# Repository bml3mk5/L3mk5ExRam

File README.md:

# External Memory Card For HITACHI BASIC MASTER LEVEL3 mark5

This is the external memory card for HITACHI BASIC MASTER LEVEL3 mark5 (MB-6892/A).

* This card is not able to use on BASIC MASTER LEVEL3 (MB-6890) and MarkII (MB-6891).

## Used Tools

* EAGLE 9.6

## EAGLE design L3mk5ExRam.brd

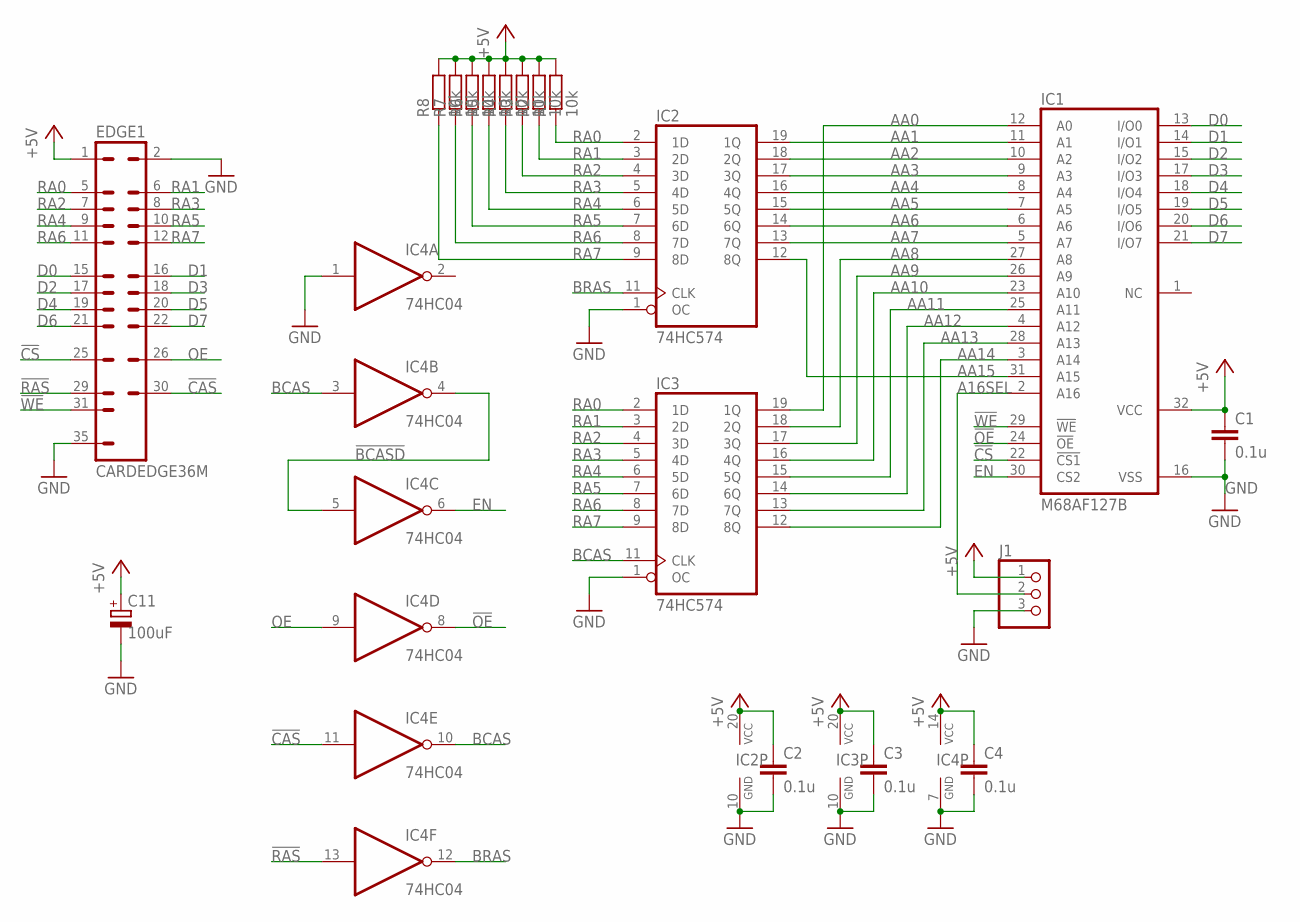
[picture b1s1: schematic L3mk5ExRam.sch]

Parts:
C1, C2, C3, C4: 0.1u; C025-024X044
C11: 100uF; E2-5
EDGE1: CARDEDGE36M; PM
IC1: M68AF127B; SOJ32-400
IC2, IC3: 74HC574; DIL20
IC4: 74HC04; DIL14
J1: PINHD-1X3; 1X03
R1, R2, R3, R4, R5, R6, R7, R8: 10k; 0204V

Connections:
!BCASD: IC4.4 (O), IC4.5 (I)
!CAS: EDGE1.30, IC4.11 (I)
!CS: EDGE1.25, IC1.22 (!CS1)
!OE: IC1.24 (!OE), IC4.8 (O)
!RAS: EDGE1.29, IC4.13 (I)
!WE: EDGE1.31, IC1.29 (!WE)
+5V: C1.1, C2.1, C3.1, C4.1, C11.+, EDGE1.1, IC1.32 (VCC), IC2.20 (VCC), IC3.20 (VCC), IC4.14 (VCC), J1.1, R1.2, R2.2, R3.2, R4.2, R5.2, R6.2, R7.2, R8.2
A16SEL: IC1.2 (A16), J1.2
AA0: IC1.12 (A0), IC3.19 (1Q)
AA1: IC1.11 (A1), IC2.19 (1Q)
AA2: IC1.10 (A2), IC2.18 (2Q)
AA3: IC1.9 (A3), IC2.17 (3Q)
AA4: IC1.8 (A4), IC2.16 (4Q)
AA5: IC1.7 (A5), IC2.15 (5Q)
AA6: IC1.6 (A6), IC2.14 (6Q)
AA7: IC1.5 (A7), IC2.13 (7Q)
AA8: IC1.27 (A8), IC3.18 (2Q)
AA9: IC1.26 (A9), IC3.17 (3Q)
AA10: IC1.23 (A10), IC3.16 (4Q)
AA11: IC1.25 (A11), IC3.15 (5Q)
AA12: IC1.4 (A12), IC3.14 (6Q)
AA13: IC1.28 (A13), IC3.13 (7Q)
AA14: IC1.3 (A14), IC3.12 (8Q)
AA15: IC1.31 (A15), IC2.12 (8Q)
BCAS: IC3.11 (CLK), IC4.3 (I), IC4.10 (O)
BRAS: IC2.11 (CLK), IC4.12 (O)
D0: EDGE1.15, IC1.13 (I/O0)
D1: EDGE1.16, IC1.14 (I/O1)
D2: EDGE1.17, IC1.15 (I/O2)
D3: EDGE1.18, IC1.17 (I/O3)
D4: EDGE1.19, IC1.18 (I/O4)
D5: EDGE1.20, IC1.19 (I/O5)
D6: EDGE1.21, IC1.20 (I/O6)
D7: EDGE1.22, IC1.21 (I/O7)
EN: IC1.30 (CS2), IC4.6 (O)
GND: C1.2, C2.2, C3.2, C4.2, C11.-, EDGE1.2, EDGE1.35, IC1.16 (VSS), IC2.1 (OC), IC2.10 (GND), IC3.1 (OC), IC3.10 (GND), IC4.1 (I), IC4.7 (GND), J1.3
OE: EDGE1.26, IC4.9 (I)
RA0: EDGE1.5, IC2.2 (1D), IC3.2 (1D), R1.1
RA1: EDGE1.6, IC2.3 (2D), IC3.3 (2D), R2.1
RA2: EDGE1.7, IC2.4 (3D), IC3.4 (3D), R3.1
RA3: EDGE1.8, IC2.5 (4D), IC3.5 (4D), R4.1
RA4: EDGE1.9, IC2.6 (5D), IC3.6 (5D), R5.1
RA5: EDGE1.10, IC2.7 (6D), IC3.7 (6D), R6.1
RA6: EDGE1.11, IC2.8 (7D), IC3.8 (7D), R7.1
RA7: EDGE1.12, IC2.9 (8D), IC3.9 (8D), R8.1

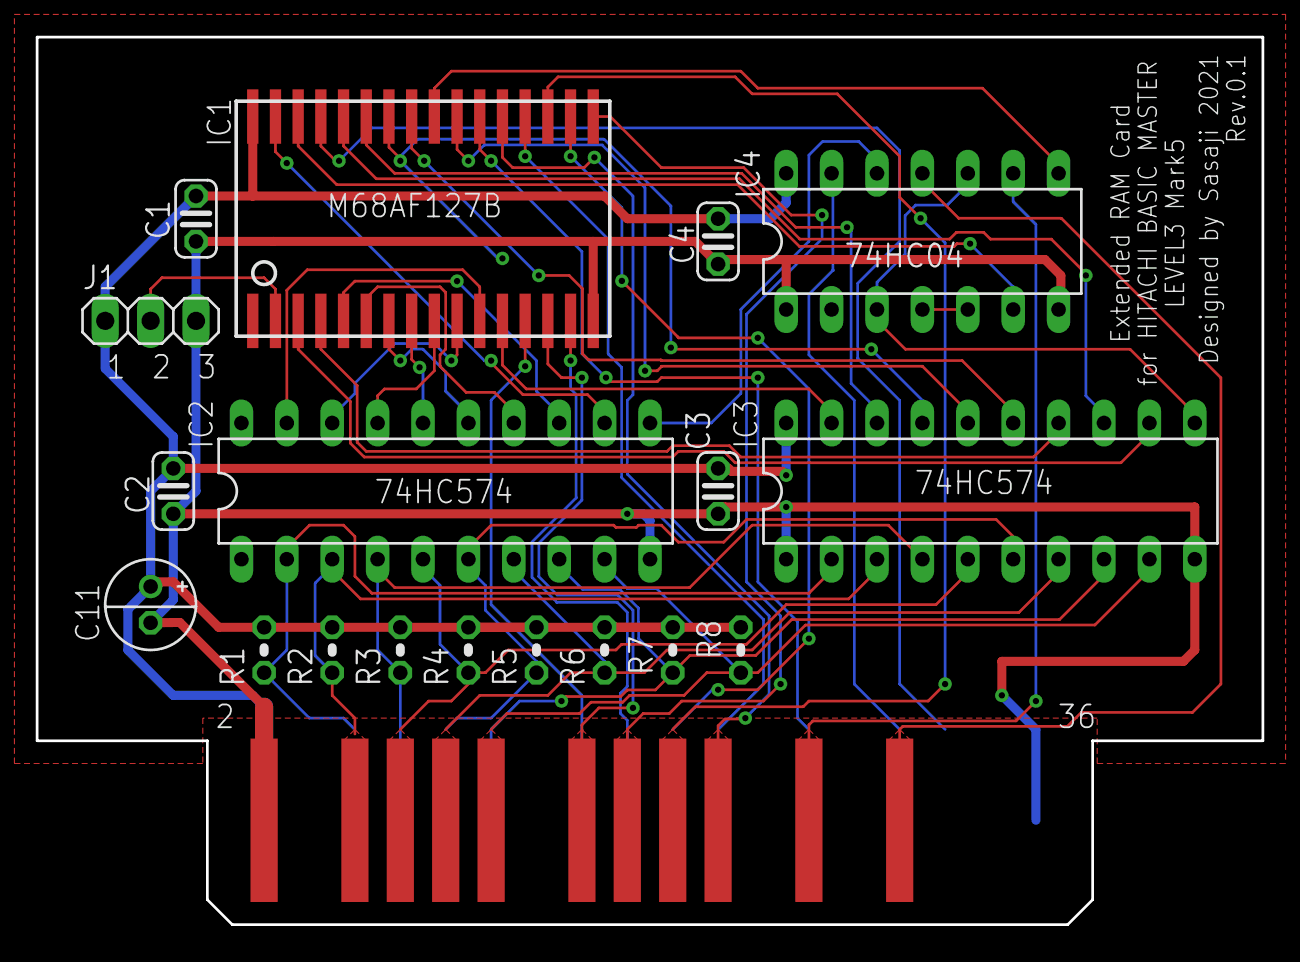
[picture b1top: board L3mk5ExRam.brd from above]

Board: 2 copper layers, 68.6 x 49.7 mm, 19 parts (0 on the bottom side), 45 nets.

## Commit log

2023-03-06 Revision 0.1
